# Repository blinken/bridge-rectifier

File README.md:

# Bench bridge rectifier

A really simple project - a bridge rectifier, with a fuse, designed to be
inserted into an aluminium case with banana plugs in and out. I wanted this to
safely dump 2A @ 250V AC into my DC electronic load (don't ask!)

The board is designed with 5mm separation between different nets.

The PCB is designed to slide in to rails in the aluminium extrusion, and the
edges of the PCB are left exposed so earth is electrically connected to the
enclosure.

## Bill of materials

 * Vishay PB5010 Bridge Rectifier, 45A, 1000V, 4-Pin (RS 180-7160)
 * 5x JST, VH, B2P, 2 Way, 1 Row, Straight PCB Header
 * Schurter 10A PCB Mount Fuse Holder 0031.8201 (RS 176-9047)
 * H100CHDL LED (RS 752-9084)
 * 1N4007 diode
 * 220k resistor, 0.25W or 0.5W
 * An aluminium extrusion case suitable for a 70x114mm board - eg, [AliExpress](https://www.aliexpress.com/item/1005003326971939.html)

## License

[CC BY-SA 3.0](https://creativecommons.org/licenses/by-sa/3.0/)

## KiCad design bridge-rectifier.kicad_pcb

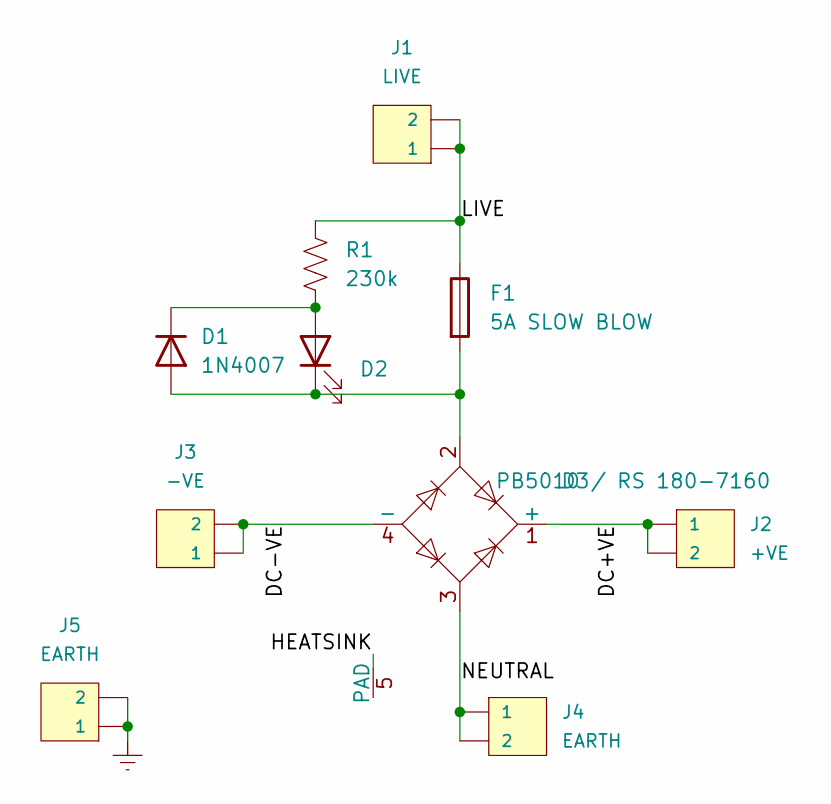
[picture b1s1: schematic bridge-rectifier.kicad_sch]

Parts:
D1: 1N4007; D_DO-41_SOD81_P10.16mm_Horizontal
D2: H100CHDLRS 752-9084; LED_D1.8mm_W1.8mm_H2.4mm_Horizontal_O1.27mm_Z1.6mm
D3: PB5010 / RS 180-7160; Vishay_Diode_Bridge_Rectifier_PB
F1: 5A SLOW BLOW; Fuseholder_Cylinder-5x20mm_Schurter_0031_8201_Horizontal_Op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
J1: LIVE; JST_VH_B2P-VH_1x02_P3.96mm_Vertical; LCSC C131337
J2: +VE; JST_VH_B2P-VH_1x02_P3.96mm_Vertical; LCSC C131337
J3: -VE; JST_VH_B2P-VH_1x02_P3.96mm_Vertical; LCSC C131337
J4, J5: EARTH; JST_VH_B2P-VH_1x02_P3.96mm_Vertical; LCSC C131337
R1: 230k; R_Axial_DIN0207_L6.3mm_D2.5mm_P10.16mm_Horizontal

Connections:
/DC+VE: D3.1 (+), J2.1, J2.2
/DC-VE: D3.4 (-), J3.1, J3.2
/HEATSINK: D3.5 (PAD)
/LIVE: F1.1, J1.1, J1.2, R1.1
/NEUTRAL: D3.3, J4.1, J4.2
Earth: J5.1, J5.2
unnamed: D1.1 (K), D2.2 (A), R1.2
unnamed: D1.2 (A), D2.1 (K), D3.2, F1.2

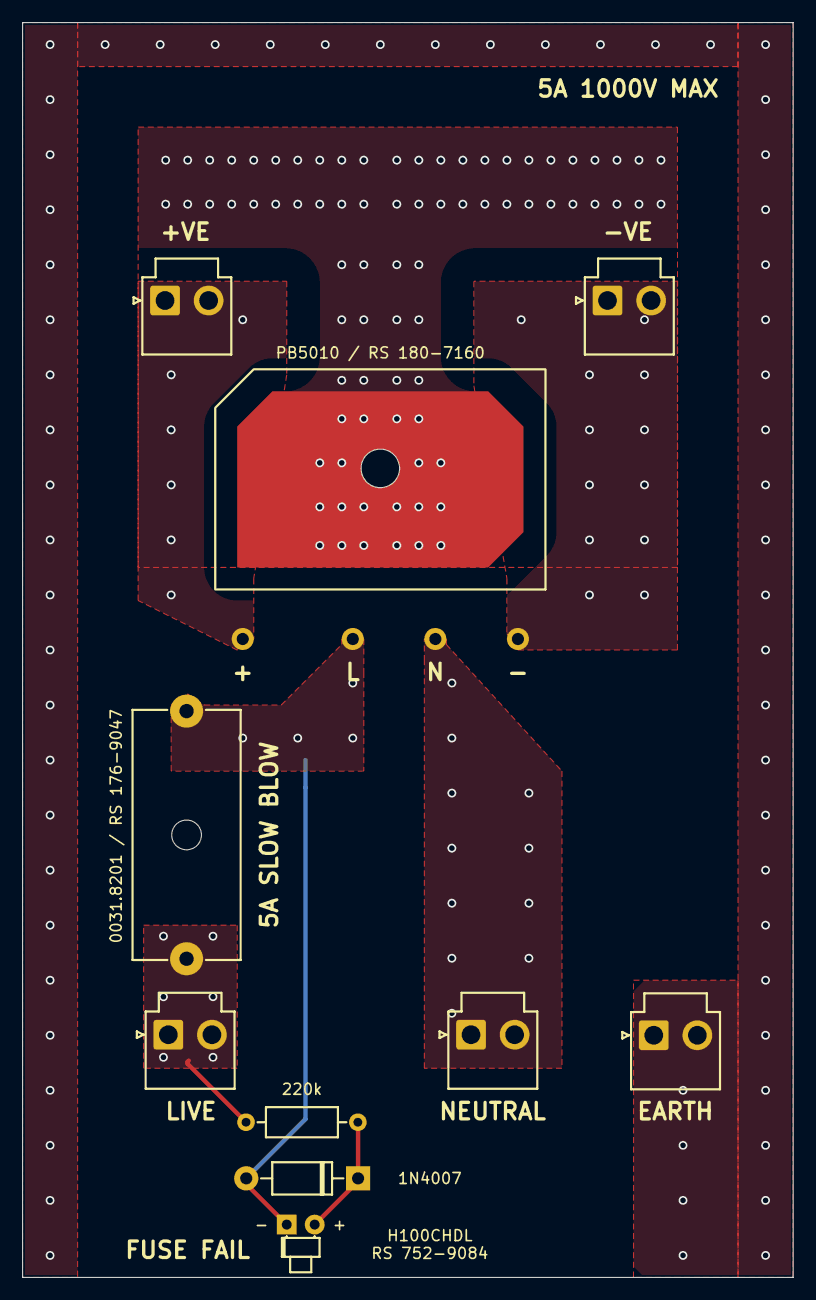
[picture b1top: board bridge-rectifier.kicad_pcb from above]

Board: 2 copper layers, 70.0 x 114.0 mm, 10 parts (0 on the bottom side), 7 nets.

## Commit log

2023-07-14 bridge rectifier v1.0
2023-07-15 Add README, LICENSE, case images
2023-07-15 Fix markdown links, add gitignore
2023-07-15 Add PCB render
2023-07-15 Add comment about earth connection
2023-07-15 Change resistor to a standard value & remove unnecessary dimension
